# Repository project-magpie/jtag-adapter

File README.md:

JTAG - Adapter
==============

FTDI4232H mini module STM Microconnect Light clone JTAG adapter this is based on the information
provided by [Avi+ Repair tips forum](http://www.avi-plus.com/categories/repair-tips-forum/repair-tips-forum/st40-stb71xx-jtag-interfacing.html).

The eagle files provide the JTAG breakout of the FTDI4232 chip.

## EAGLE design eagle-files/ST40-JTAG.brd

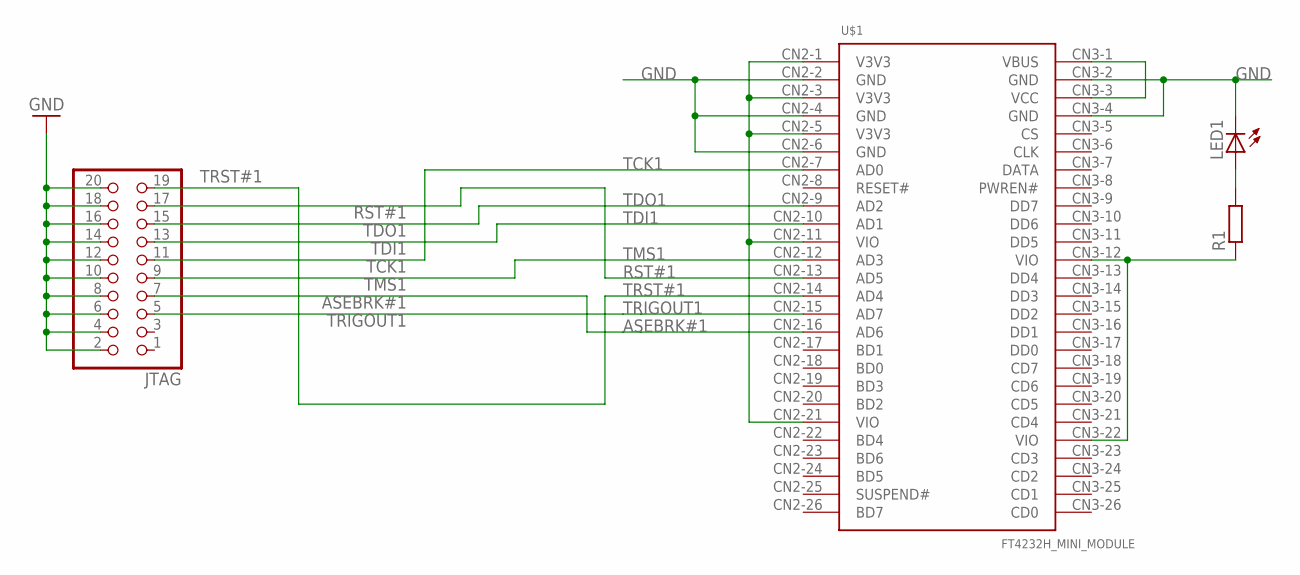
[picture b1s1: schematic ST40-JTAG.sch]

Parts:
JTAG: PINHD-2X10; 2X10
LED1: LED1206; LED-1206
R1: R-EU_M0805; M0805
U$1: FT4232H_MINI_MODULE; PINHEAD

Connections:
ASEBRK#1: JTAG.7, U$1.CN2-16 (AD6)
GND: JTAG.2, JTAG.4, JTAG.6, JTAG.8, JTAG.10, JTAG.12, JTAG.14, JTAG.16, JTAG.18, JTAG.20, LED1.C, U$1.CN2-2 (GND), U$1.CN2-4 (GND), U$1.CN2-6 (GND), U$1.CN3-2 (GND), U$1.CN3-4 (GND)
unnamed: U$1.CN3-1 (VBUS), U$1.CN3-3 (VCC)
unnamed: U$1.CN2-1 (V3V3), U$1.CN2-3 (V3V3), U$1.CN2-5 (V3V3), U$1.CN2-11 (VIO)
unnamed: R1.1, U$1.CN3-12 (VIO), U$1.CN3-22 (VIO)
unnamed: LED1.A, R1.2
RST#1: JTAG.17, U$1.CN2-13 (AD5)
TCK1: JTAG.11, U$1.CN2-7 (AD0)
TDI1: JTAG.13, U$1.CN2-10 (AD1)
TDO1: JTAG.15, U$1.CN2-9 (AD2)
TMS1: JTAG.9, U$1.CN2-12 (AD3)
TRIGOUT1: JTAG.5, U$1.CN2-15 (AD7)
TRST#1: JTAG.19, U$1.CN2-14 (AD4)

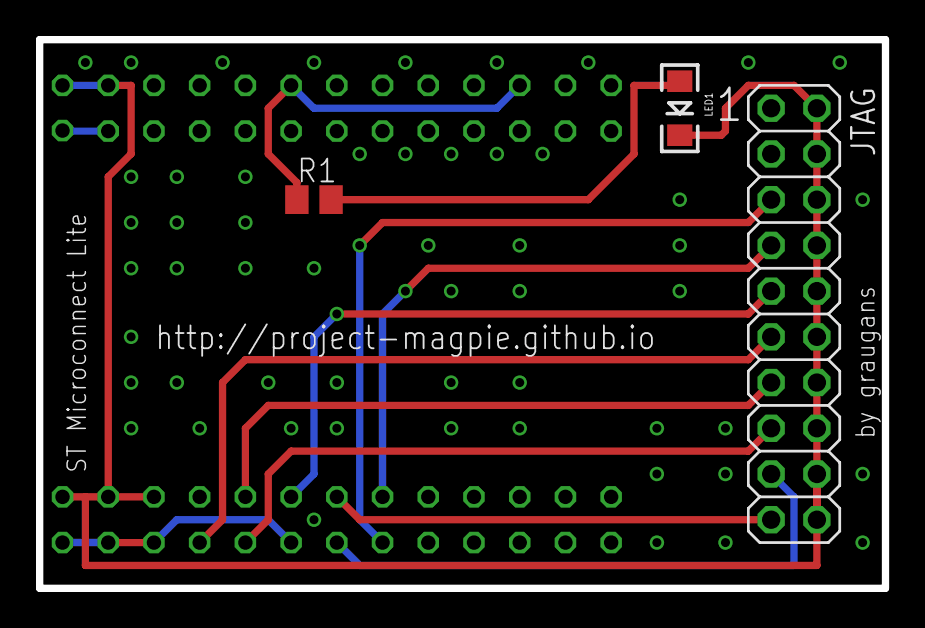
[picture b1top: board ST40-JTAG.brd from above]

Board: 4 copper layers, 47.0 x 30.5 mm, 4 parts (0 on the bottom side), 13 nets.

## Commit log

2014-06-15 Added basic eagle library for FTDI 4232 mini module
2014-06-15 Added eagle files for the STM Microconnect Clone
    This clone is build arround the FTDI FT4232 mini module.
2014-06-15 Added PDF versions of board and schematic
2014-06-15 Added some basic information

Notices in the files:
parts and their libraries:
SparkFun-LED: Licensing: Creative Commons ShareAlike 4.0 International - https://creativecommons.org/licenses/by-sa/4.0
